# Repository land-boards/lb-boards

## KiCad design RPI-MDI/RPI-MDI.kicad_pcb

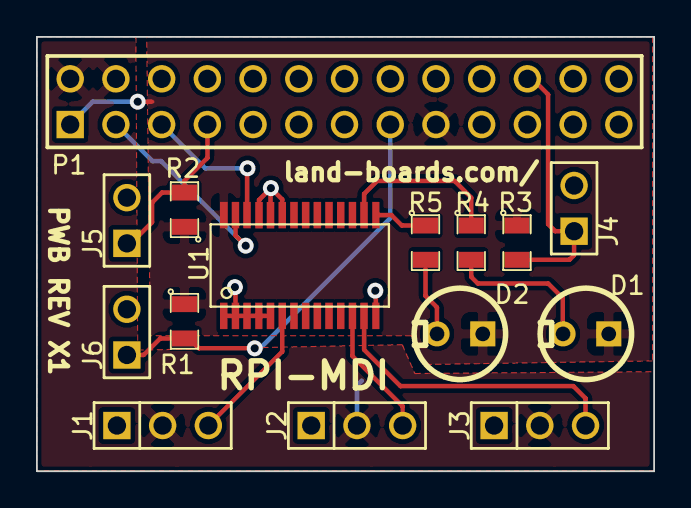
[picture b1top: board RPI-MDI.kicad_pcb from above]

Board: 2 copper layers, 34.3 x 24.1 mm, 16 parts (1 on the bottom side), 15 nets.

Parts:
C1: 106; SM1206
D1, D2: LED; LEDV
J1, J2, J3: CONN_3; PIN_ARRAY_3X1
J4, J5, J6: CONN_2; PIN_ARRAY_2X1
P1: RASPIO; pin_array_13x2
R1, R2, R3: 4.7K; SM0805
R4, R5: 120; SM0805
U1: PCA9685; tssop-28

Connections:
/+3.3V: D1.1, D2.1, P1.1, P1.17, R1.1, R2.1, R3.1, U1.28
/IO_4: J5.1, P1.7, R2.2
/IO_22: J6.1, P1.15, R1.2
/IO_25: J4.1, P1.22, R3.2
/R5: C1.1, J1.2, J2.2, J3.2, P1.2, P1.4
/SCLK1: P1.5, U1.26
/SDA1: P1.3, U1.27
GND: C1.2, J1.1, J2.1, J3.1, J4.2, J5.2, J6.2, P1.6, P1.9, P1.14, P1.20, P1.25, U1.1, U1.2, U1.3, U1.4, U1.5, U1.14, U1.23, U1.24, U1.25
unnamed: J2.3, U1.12
unnamed: J3.3, U1.13
unnamed: J1.3, U1.6
unnamed: R4.1, U1.16
unnamed: R5.1, U1.15
unnamed: D1.2, R4.2
unnamed: D2.2, R5.2

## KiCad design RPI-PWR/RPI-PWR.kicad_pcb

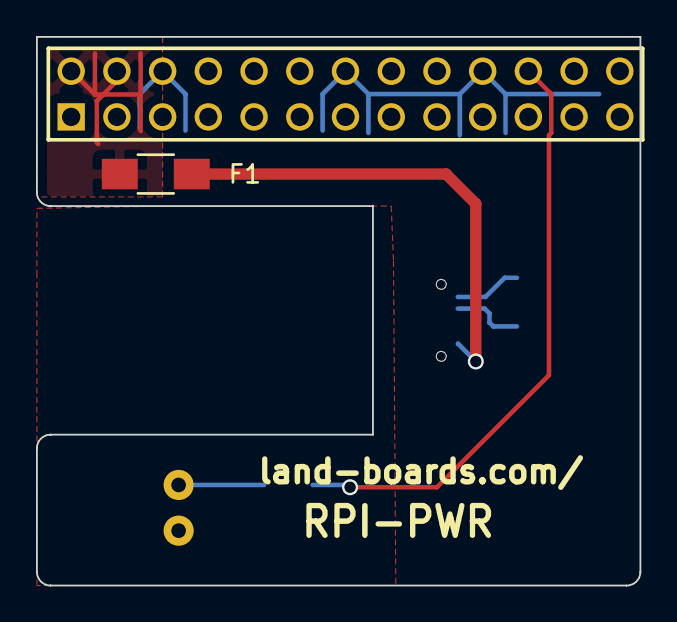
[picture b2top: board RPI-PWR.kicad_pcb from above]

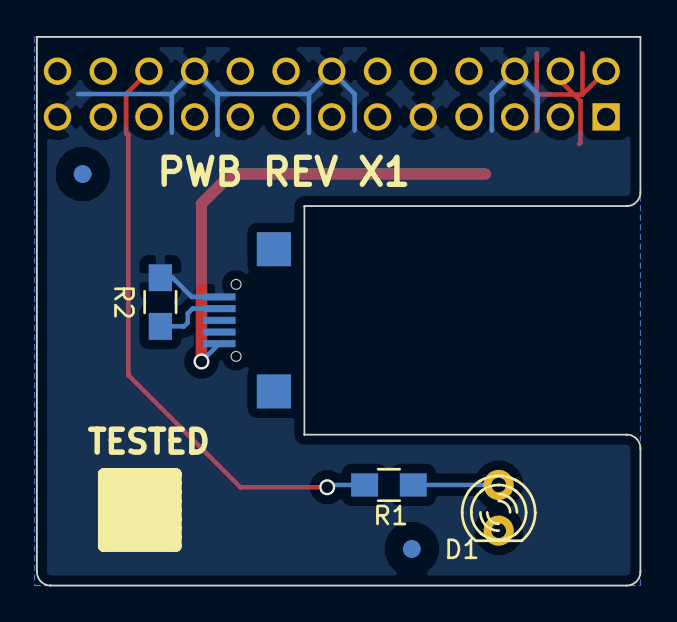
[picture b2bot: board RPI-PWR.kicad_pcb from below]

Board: 2 copper layers, 33.5 x 30.5 mm, 9 parts (7 on the bottom side), 6 nets.

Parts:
D1: LED; LED-3MM
F1: FUSE; R_1206_HandSoldering
FID1, FID2: CONN_1; FIDUCIAL
J1: USB-MICRO-B; USB_Micro-B-Wellco-SMT
J2: RASPIO; pin_array_13x2
R1: 270; R_0805_HandSoldering
R2: 130K; R_0805_HandSoldering
TESTED: COUPON; REV_BLOCK

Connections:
/+5V: F1.1, J2.2, J2.4
/+5V-USB: F1.2, J1.1
/GND: J1.5, J2.6, J2.9, J2.14, J2.20, J2.25, R2.2
/PUP0: D1.1, R1.2
unnamed: J1.4, R2.1
unnamed: J2.22, R1.1

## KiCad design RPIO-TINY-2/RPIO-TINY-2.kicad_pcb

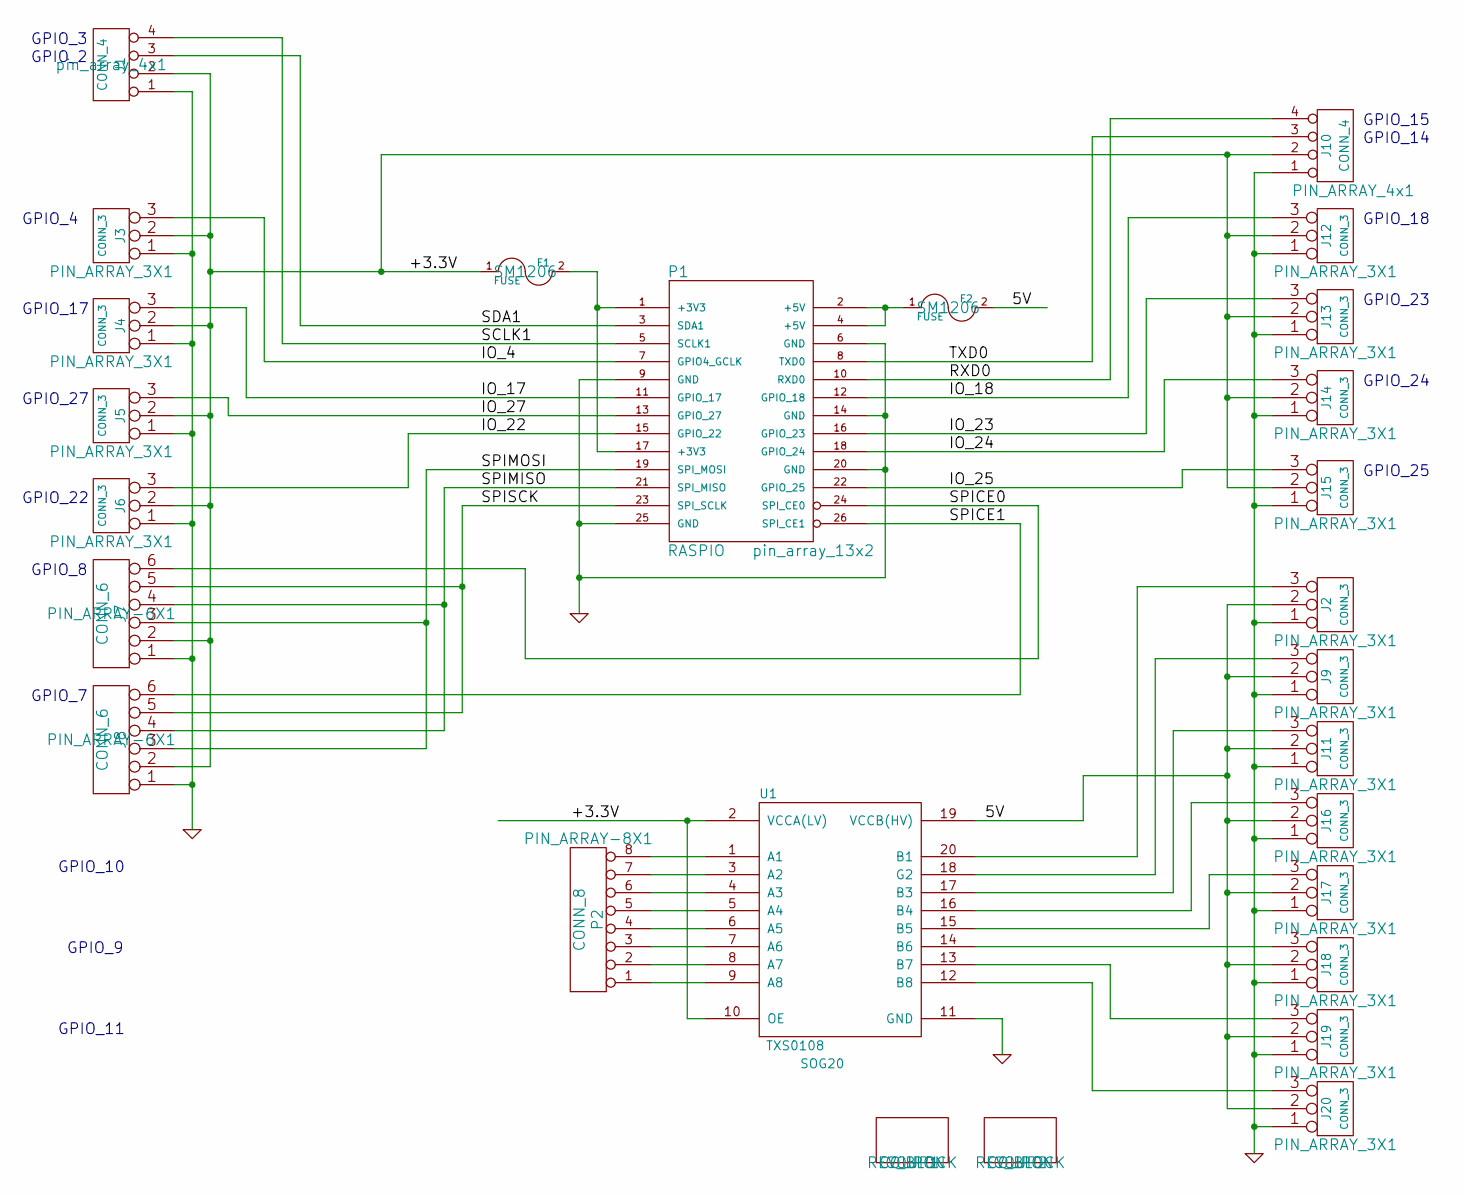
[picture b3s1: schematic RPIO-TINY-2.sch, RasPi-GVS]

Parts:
COUP1, COUP2: COUPON; REV_BLOCK
F1, F2: FUSE; SM1206
J1: CONN_4; pin_array_4x1
J2, J3, J4, J5, J6, J9, J11, J12, J13, J14, J15, J16, J17, J18, J19, J20: CONN_3; PIN_ARRAY_3X1
J7, J8: CONN_6; PIN_ARRAY-6X1
J10: CONN_4; PIN_ARRAY_4x1
P1: RASPIO; pin_array_13x2
P2: CONN_8; PIN_ARRAY-8X1
U1: TXS0108; SOG20

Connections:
/5V: F2.2, J2.2 (PM), J9.2 (PM), J11.2 (PM), J16.2 (PM), J17.2 (PM), J18.2 (PM), J19.2 (PM), J20.2 (PM), U1.19 (VCCB(HV))
/+3.3V: F1.1, J1.2, J3.2 (PM), J4.2 (PM), J5.2 (PM), J6.2 (PM), J7.2, J8.2, J10.2, J12.2 (PM), J13.2 (PM), J14.2 (PM), J15.2 (PM), U1.2 (VCCA(LV)), U1.10 (OE)
/IO_4: J3.3, P1.7 (GPIO4_GCLK)
/IO_17: J4.3, P1.11 (GPIO_17)
/IO_18: J12.3, P1.12 (GPIO_18)
/IO_22: J6.3, P1.15 (GPIO_22)
/IO_23: J13.3, P1.16 (GPIO_23)
/IO_24: J14.3, P1.18 (GPIO_24)
/IO_25: J15.3, P1.22 (GPIO_25)
/IO_27: J5.3, P1.13 (GPIO_27)
/RXD0: J10.4, P1.10 (RXD0)
/SCLK1: J1.4, P1.5 (SCLK1)
/SDA1: J1.3, P1.3 (SDA1)
/SPICE0: J7.6, P1.24 (SPI_CE0)
/SPICE1: J8.6, P1.26 (SPI_CE1)
/SPIMISO: J7.4, J8.4, P1.21 (SPI_MISO)
/SPIMOSI: J7.3, J8.3, P1.19 (SPI_MOSI)
/SPISCK: J7.5, J8.5, P1.23 (SPI_SCLK)
/TXD0: J10.3, P1.8 (TXD0)
GND: J1.1, J2.1, J3.1, J4.1, J5.1, J6.1, J7.1, J8.1, J9.1, J10.1, J11.1, J12.1, J13.1, J14.1, J15.1, J16.1, J17.1, J18.1, J19.1, J20.1, P1.6 (GND), P1.9 (GND), P1.14 (GND), P1.20 (GND), P1.25 (GND), U1.11 (GND)
unnamed: J17.3, U1.15 (B5)
unnamed: J18.3, U1.14 (B6)
unnamed: J19.3, U1.13 (B7)
unnamed: J20.3, U1.12 (B8)
unnamed: J2.3, U1.20 (B1)
unnamed: J9.3, U1.18 (G2)
unnamed: J11.3, U1.17 (B3)
unnamed: J16.3, U1.16 (B4)
unnamed: P2.3, U1.7 (A6)
unnamed: P2.1, U1.9 (A8)
unnamed: P2.2, U1.8 (A7)
unnamed: P2.4, U1.6 (A5)
unnamed: P2.5, U1.5 (A4)
unnamed: P2.6, U1.4 (A3)
unnamed: P2.7, U1.3 (A2)
unnamed: P2.8, U1.1 (A1)
unnamed: F2.1, P1.2 (+5V), P1.4 (+5V)
unnamed: F1.2, P1.1 (+3V3), P1.17 (+3V3)

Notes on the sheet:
GPIO_2
GPIO_3
GPIO_4
GPIO_17
GPIO_27
GPIO_22
GPIO_10
GPIO_9
GPIO_11
GPIO_14
GPIO_15
GPIO_18
GPIO_23
GPIO_24
GPIO_25
GPIO_8
GPIO_7

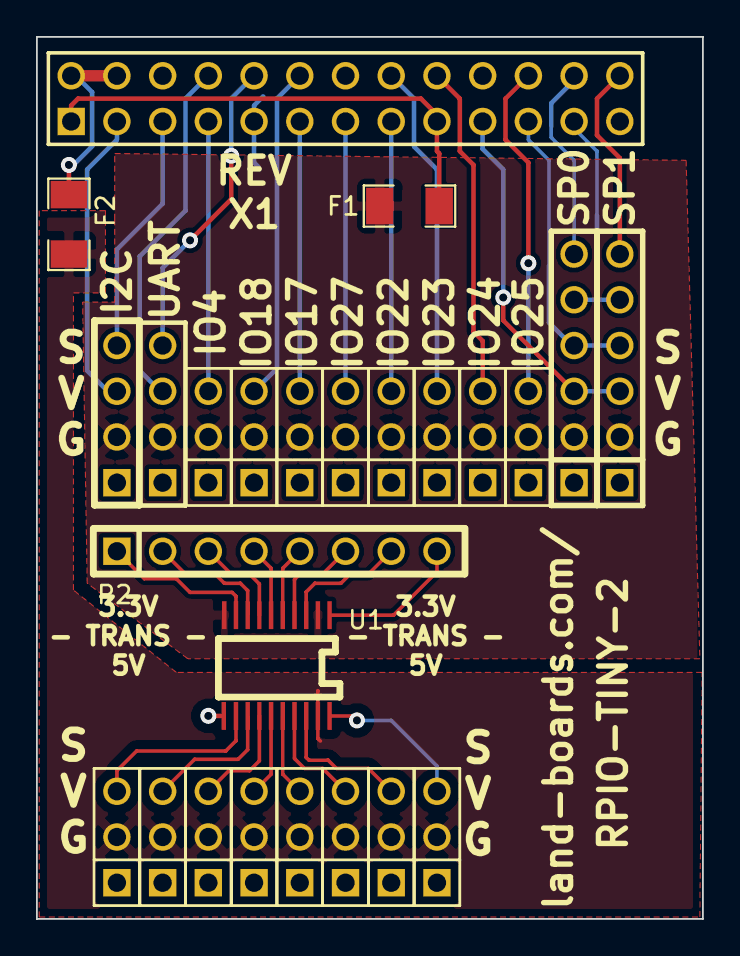
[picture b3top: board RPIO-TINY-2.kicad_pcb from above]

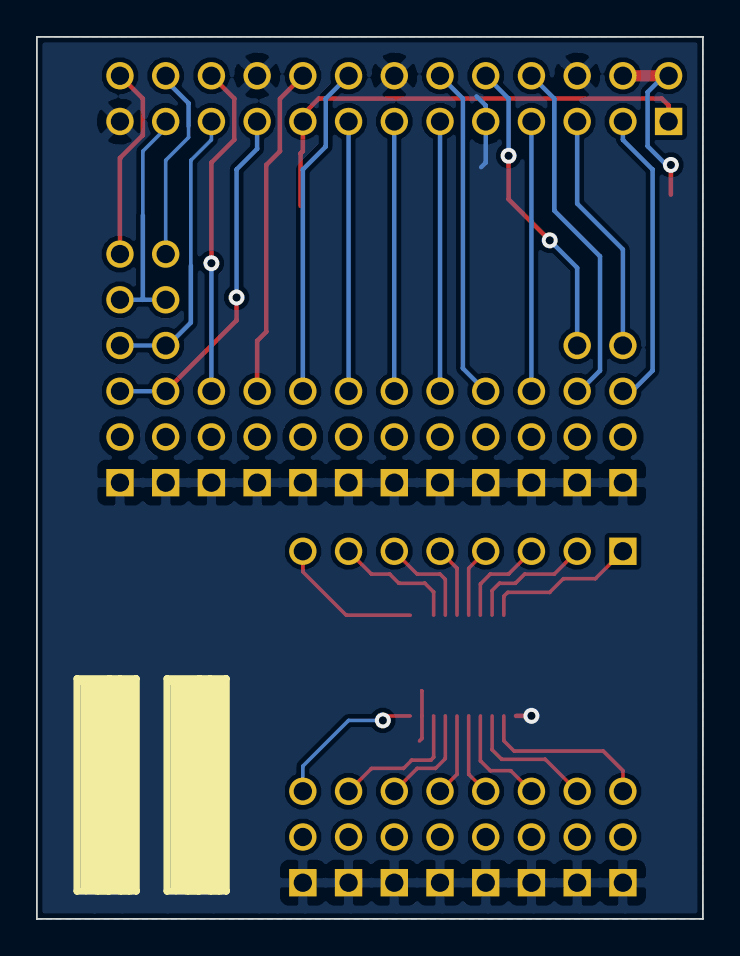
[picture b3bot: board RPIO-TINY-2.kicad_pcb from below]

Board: 2 copper layers, 37.0 x 49.0 mm, 27 parts (2 on the bottom side), 38 nets.

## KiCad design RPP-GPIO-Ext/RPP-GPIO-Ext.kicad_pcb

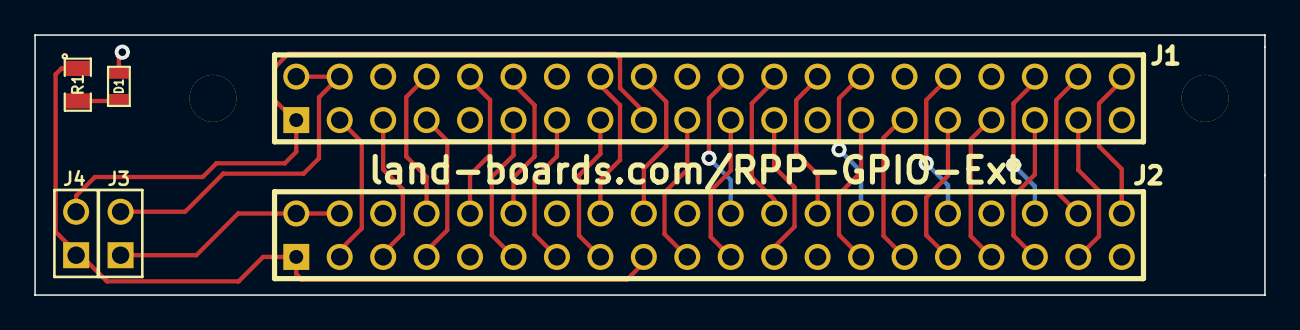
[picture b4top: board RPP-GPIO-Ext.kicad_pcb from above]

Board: 2 copper layers, 71.9 x 15.2 mm, 8 parts (0 on the bottom side), 34 nets.

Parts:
D1: LED; SM0603
J1, J2: RASPIOPLUS; PIN_ARRAY_20X2
J3, J4: CONN_2; PIN_ARRAY_2X1
MTG1, MTG2: CONN_1; MTG-2.75MM
R1: R; SM0805

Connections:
/+3.3V-1: J2.1, J2.17, J4.1, R1.1
/+3.3V-2: J1.1, J1.17, J4.2
/GND: D1.2, J1.6, J1.9, J1.14, J1.20, J1.25, J1.30, J1.34, J1.39, J2.6, J2.9, J2.14, J2.20, J2.25, J2.30, J2.34, J2.39
/ID_SC: J1.28, J2.28
/ID_SD: J1.27, J2.27
/IO_4: J1.7, J2.7
/IO_5: J1.29, J2.29
/IO_6: J1.31, J2.31
/IO_12: J1.32, J2.32
/IO_13: J1.33, J2.33
/IO_16: J1.36, J2.36
/IO_17: J1.11, J2.11
/IO_18: J1.12, J2.12
/IO_19: J1.35, J2.35
/IO_20: J1.38, J2.38
/IO_21: J1.40, J2.40
/IO_22: J1.15, J2.15
/IO_23: J1.16, J2.16
/IO_24: J1.18, J2.18
/IO_25: J1.22, J2.22
/IO_26: J1.37, J2.37
/IO_27: J1.13, J2.13
/R5-1: J2.2, J2.4, J3.1
/R5-2: J1.2, J1.4, J3.2
/RXD0: J1.10, J2.10
/SCLK1: J1.5, J2.5
/SDA1: J1.3, J2.3
/SPICE0: J1.24, J2.24
/SPICE1: J1.26, J2.26
/SPIMISO: J1.21, J2.21
/SPIMOSI: J1.19, J2.19
/SPISCK: J1.23, J2.23
/TXD0: J1.8, J2.8
unnamed: D1.1, R1.2

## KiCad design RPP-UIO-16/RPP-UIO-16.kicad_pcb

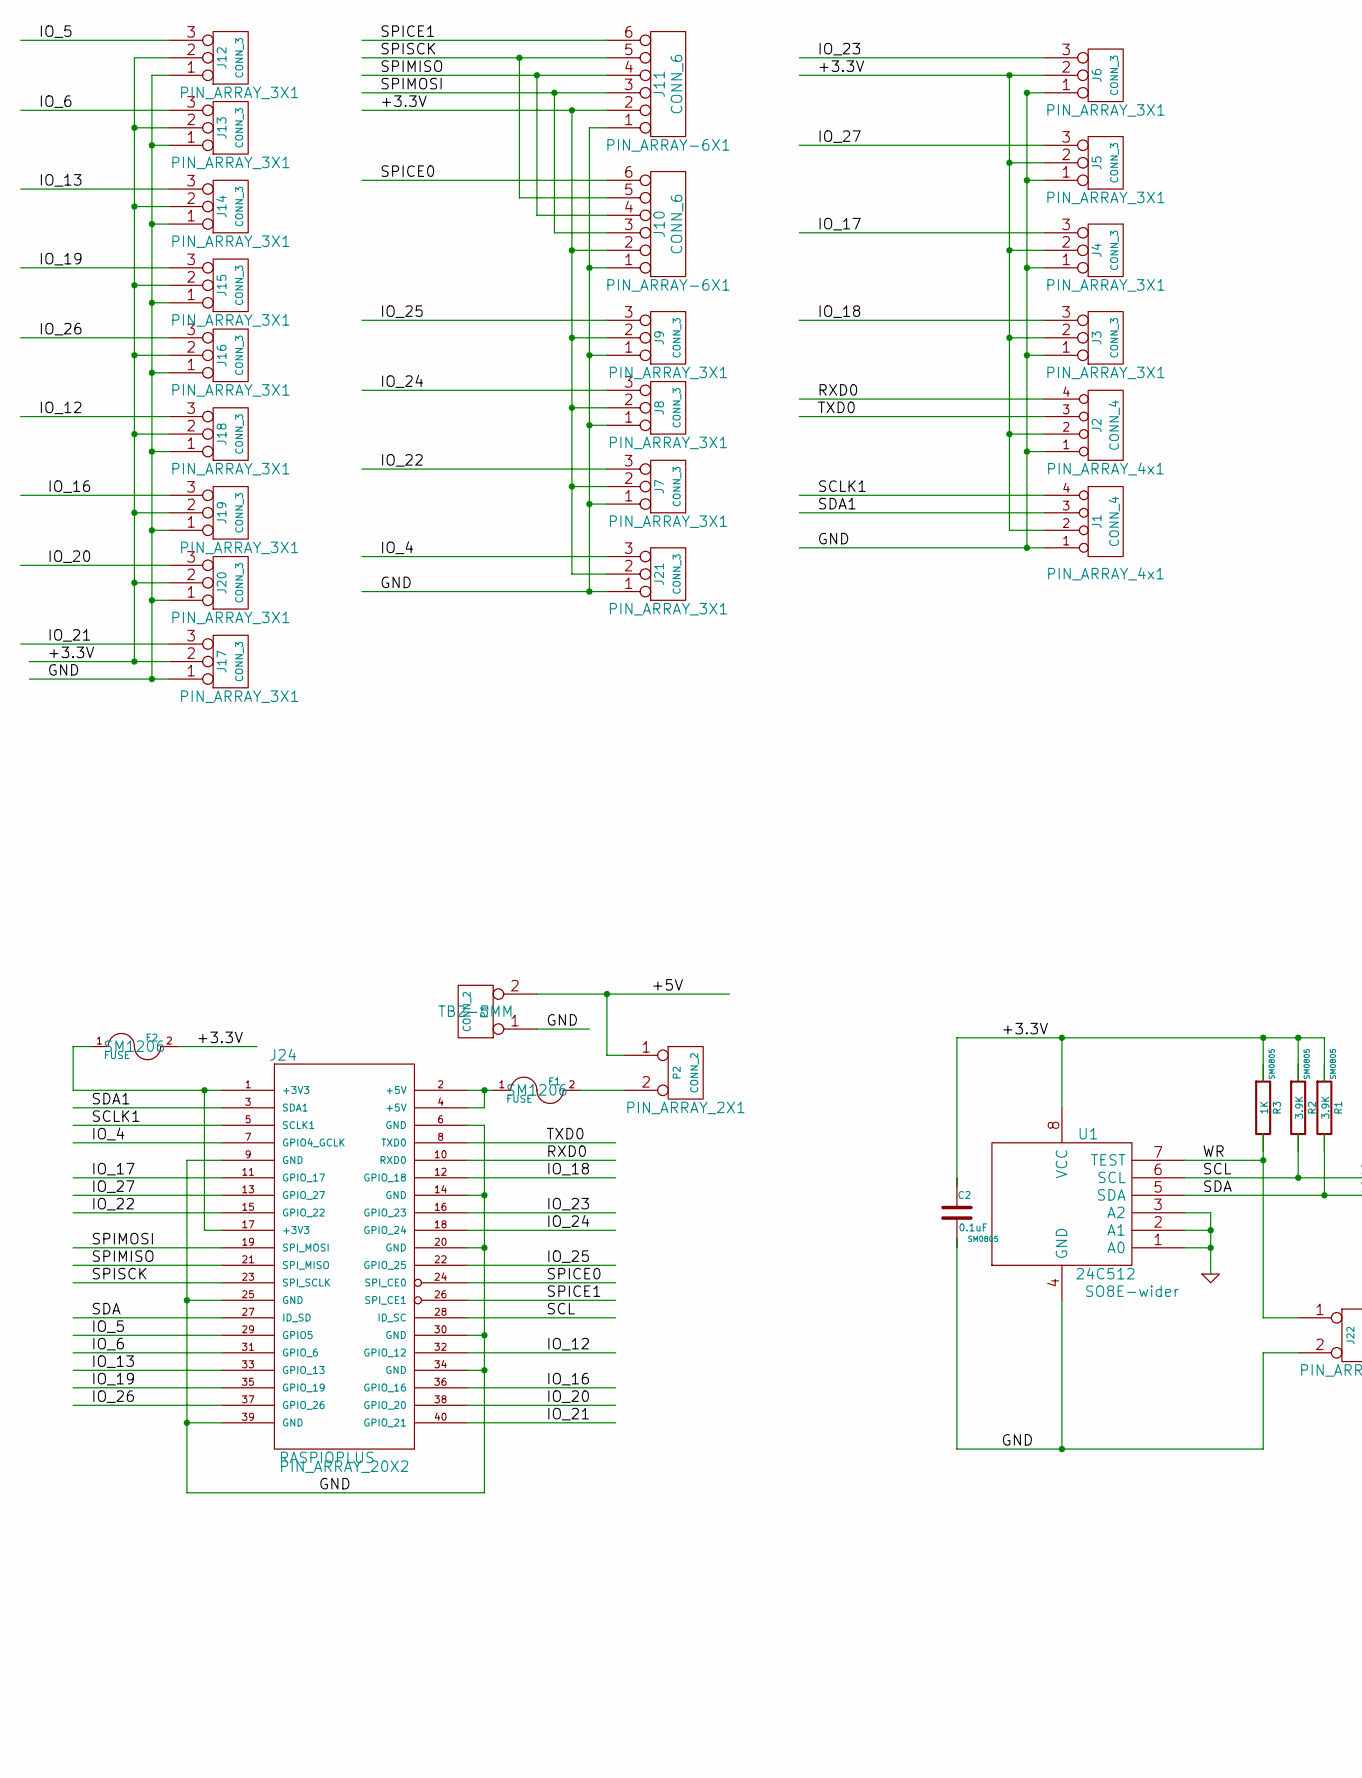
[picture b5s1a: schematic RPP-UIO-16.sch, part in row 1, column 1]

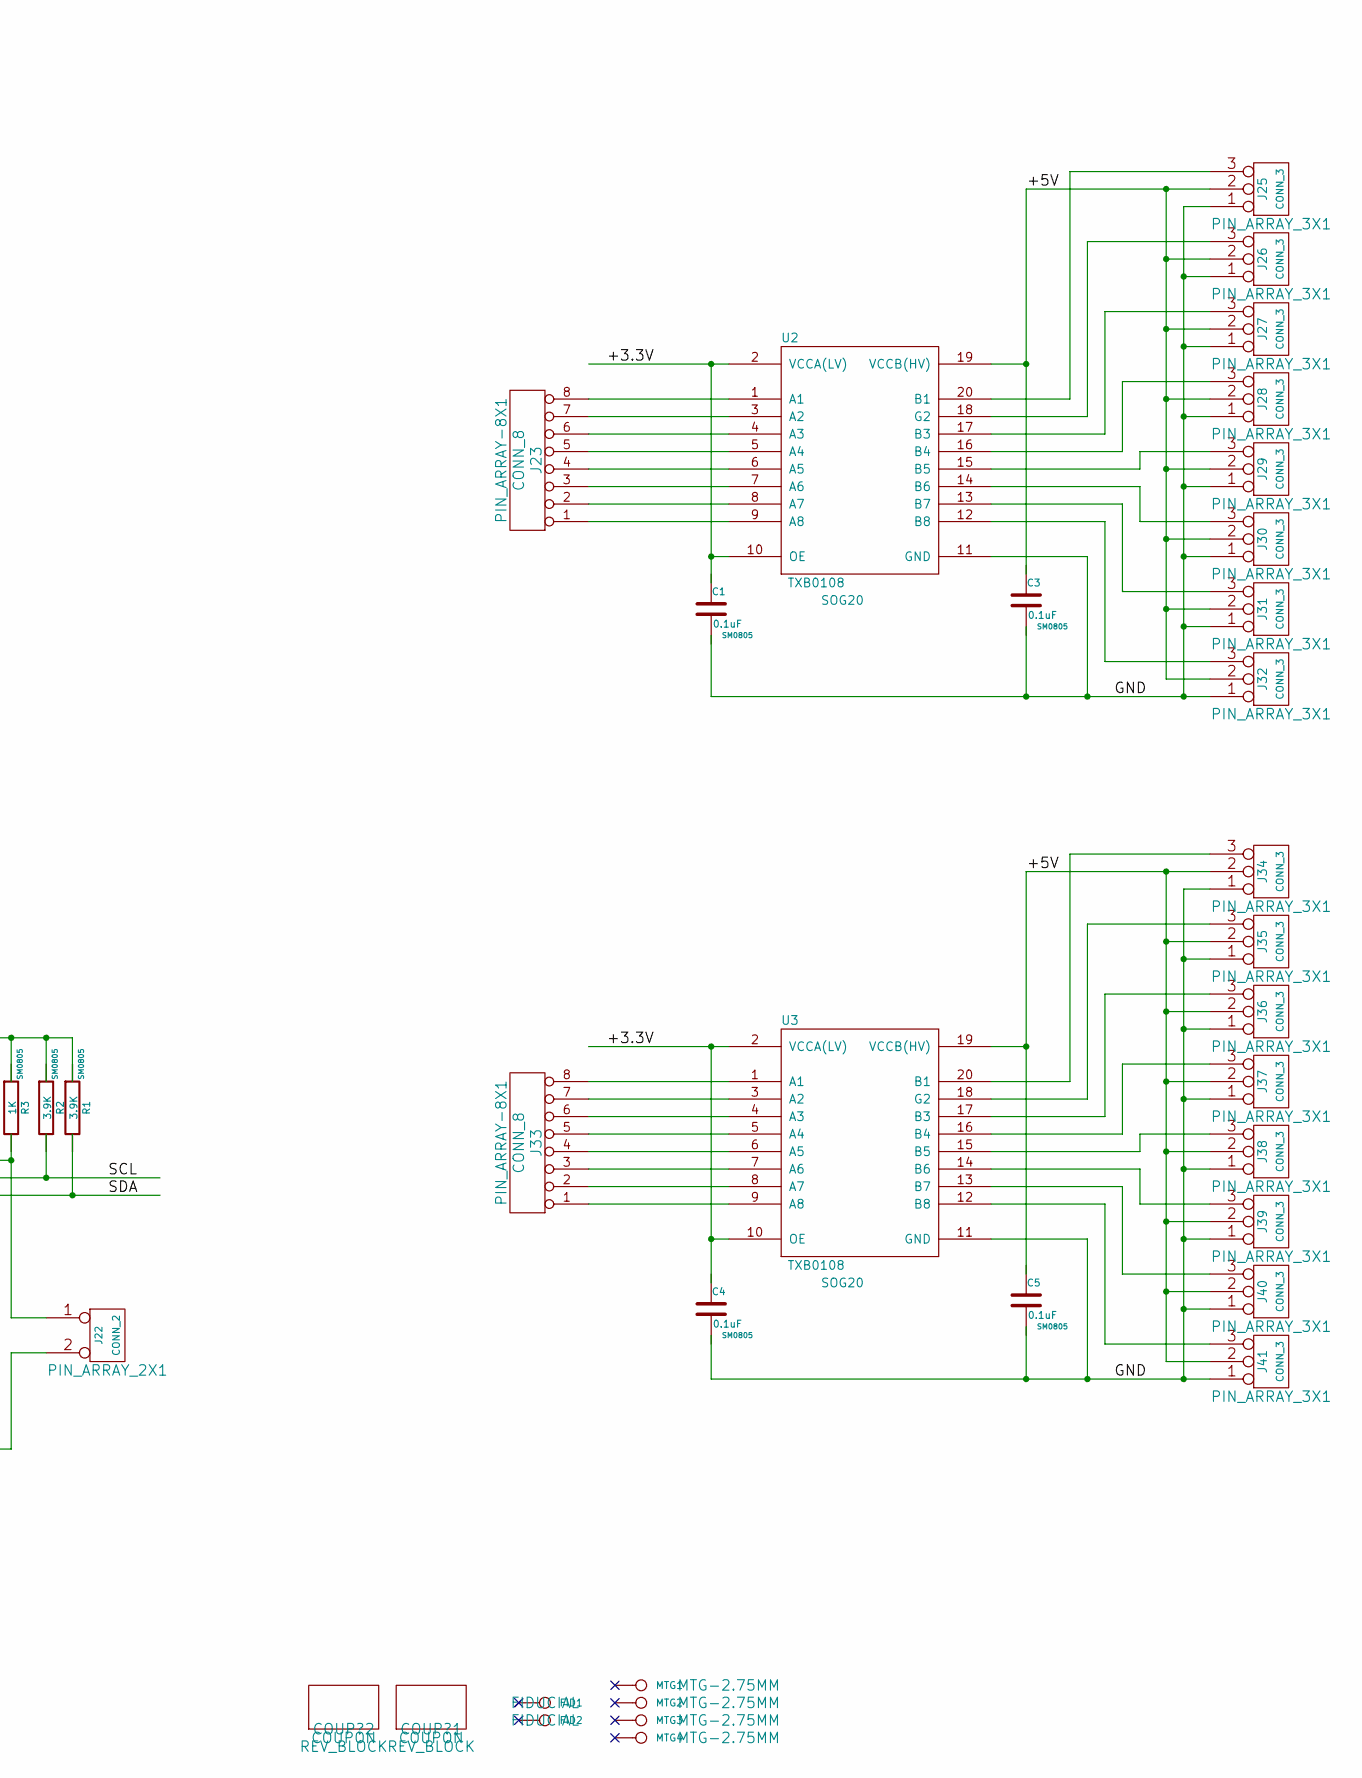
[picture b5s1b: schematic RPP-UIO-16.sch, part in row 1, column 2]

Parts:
C1, C2, C3, C4, C5: 0.1uF; SM0805
COUP?1, COUP?2: COUPON; REV_BLOCK
F1, F2: FUSE; SM1206
FID1, FID2: CONN_1; FIDUCIAL
J1, J2: CONN_4; PIN_ARRAY_4x1
J3, J4, J5, J6, J7, J8, J9, J12, J13, J14, J15, J16, J17, J18, J19, J20, J21, J25, J26, J27, J28, J29, J30, J31, J32, J34, J35, J36, J37, J38, J39, J40, J41: CONN_3; PIN_ARRAY_3X1
J10, J11: CONN_6; PIN_ARRAY-6X1
J22: CONN_2; PIN_ARRAY_2X1
J23, J33: CONN_8; PIN_ARRAY-8X1
J24: RASPIOPLUS; PIN_ARRAY_20X2
MTG1, MTG2, MTG3, MTG4: CONN_1; MTG-2.75MM
P1: CONN_2; TB2-5MM
P2: CONN_2; PIN_ARRAY_2X1
R1, R2: 3.9K; SM0805
R3: 1K; SM0805
U1: 24C512; SO8E-wider
U2, U3: TXB0108; SOG20

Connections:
/+3.3V: C1.1, C2.1, C4.1, F2.2, J1.2, J2.2, J3.2 (PM), J4.2 (PM), J5.2 (PM), J6.2 (PM), J7.2 (PM), J8.2 (PM), J9.2 (PM), J10.2, J11.2, J12.2 (PM), J13.2 (PM), J14.2 (PM), J15.2 (PM), J16.2 (PM), J17.2 (PM), J18.2 (PM), J19.2 (PM), J20.2 (PM), J21.2 (PM), R1.1, R2.1, R3.1, U1.8 (VCC), U2.2 (VCCA(LV)), U2.10 (OE), U3.2 (VCCA(LV)), U3.10 (OE)
/+5V: C3.1, C5.1, J25.2 (PM), J26.2 (PM), J27.2 (PM), J28.2 (PM), J29.2 (PM), J30.2 (PM), J31.2 (PM), J32.2 (PM), J34.2 (PM), J35.2 (PM), J36.2 (PM), J37.2 (PM), J38.2 (PM), J39.2 (PM), J40.2 (PM), J41.2 (PM), P1.2 (PM), P2.1, U2.19 (VCCB(HV)), U3.19 (VCCB(HV))
/IO_4: J21.3, J24.7 (GPIO4_GCLK)
/IO_5: J12.3, J24.29 (GPIO5)
/IO_6: J13.3, J24.31 (GPIO_6)
/IO_12: J18.3, J24.32 (GPIO_12)
/IO_13: J14.3, J24.33 (GPIO_13)
/IO_16: J19.3, J24.36 (GPIO_16)
/IO_17: J4.3, J24.11 (GPIO_17)
/IO_18: J3.3, J24.12 (GPIO_18)
/IO_19: J15.3, J24.35 (GPIO_19)
/IO_20: J20.3, J24.38 (GPIO_20)
/IO_21: J17.3, J24.40 (GPIO_21)
/IO_22: J7.3, J24.15 (GPIO_22)
/IO_23: J6.3, J24.16 (GPIO_23)
/IO_24: J8.3, J24.18 (GPIO_24)
/IO_25: J9.3, J24.22 (GPIO_25)
/IO_26: J16.3, J24.37 (GPIO_26)
/IO_27: J5.3, J24.13 (GPIO_27)
/RXD0: J2.4, J24.10 (RXD0)
/SCL: J24.28 (ID_SC), R2.2, U1.6 (SCL)
/SCLK1: J1.4, J24.5 (SCLK1)
/SDA: J24.27 (ID_SD), R1.2, U1.5 (SDA)
/SDA1: J1.3, J24.3 (SDA1)
/SPICE0: J10.6, J24.24 (SPI_CE0)
/SPICE1: J11.6, J24.26 (SPI_CE1)
/SPIMISO: J10.4, J11.4, J24.21 (SPI_MISO)
/SPIMOSI: J10.3, J11.3, J24.19 (SPI_MOSI)
/SPISCK: J10.5, J11.5, J24.23 (SPI_SCLK)
/TXD0: J2.3, J24.8 (TXD0)
/WR: J22.1, R3.2, U1.7 (TEST)
GND: C1.2, C2.2, C3.2, C4.2, C5.2, J1.1, J2.1, J3.1, J4.1, J5.1, J6.1, J7.1, J8.1, J9.1, J10.1, J11.1, J12.1, J13.1, J14.1, J15.1, J16.1, J17.1, J18.1, J19.1, J20.1, J21.1, J22.2 (PM), J24.6 (GND), J24.9 (GND), J24.14 (GND), J24.20 (GND), J24.25 (GND), J24.30 (GND), J24.34 (GND), J24.39 (GND), J25.1, J26.1, J27.1, J28.1, J29.1, J30.1, J31.1, J32.1, J34.1, J35.1, J36.1, J37.1, J38.1, J39.1, J40.1, J41.1, P1.1, U1.1 (A0), U1.2 (A1), U1.3 (A2), U1.4 (GND), U2.11 (GND), U3.11 (GND)
unnamed: F1.1, J24.2 (+5V), J24.4 (+5V)
unnamed: F1.2, P2.2 (PM)
unnamed: F2.1, J24.1 (+3V3), J24.17 (+3V3)
unnamed: J23.1, U2.9 (A8)
unnamed: J23.2, U2.8 (A7)
unnamed: J23.3, U2.7 (A6)
unnamed: J23.4, U2.6 (A5)
unnamed: J23.5, U2.5 (A4)
unnamed: J23.6, U2.4 (A3)
unnamed: J23.7, U2.3 (A2)
unnamed: J23.8, U2.1 (A1)
unnamed: J25.3, U2.20 (B1)
unnamed: J26.3, U2.18 (G2)
unnamed: J27.3, U2.17 (B3)
unnamed: J28.3, U2.16 (B4)
unnamed: J29.3, U2.15 (B5)
unnamed: J30.3, U2.14 (B6)
unnamed: J31.3, U2.13 (B7)
unnamed: J32.3, U2.12 (B8)
unnamed: J33.1, U3.9 (A8)
unnamed: J33.2, U3.8 (A7)
unnamed: J33.3, U3.7 (A6)
unnamed: J33.4, U3.6 (A5)
unnamed: J33.5, U3.5 (A4)
unnamed: J33.6, U3.4 (A3)
unnamed: J33.7, U3.3 (A2)
unnamed: J33.8, U3.1 (A1)
unnamed: J34.3, U3.20 (B1)
unnamed: J35.3, U3.18 (G2)
unnamed: J36.3, U3.17 (B3)
unnamed: J37.3, U3.16 (B4)
unnamed: J38.3, U3.15 (B5)
unnamed: J39.3, U3.14 (B6)
unnamed: J40.3, U3.13 (B7)
unnamed: J41.3, U3.12 (B8)

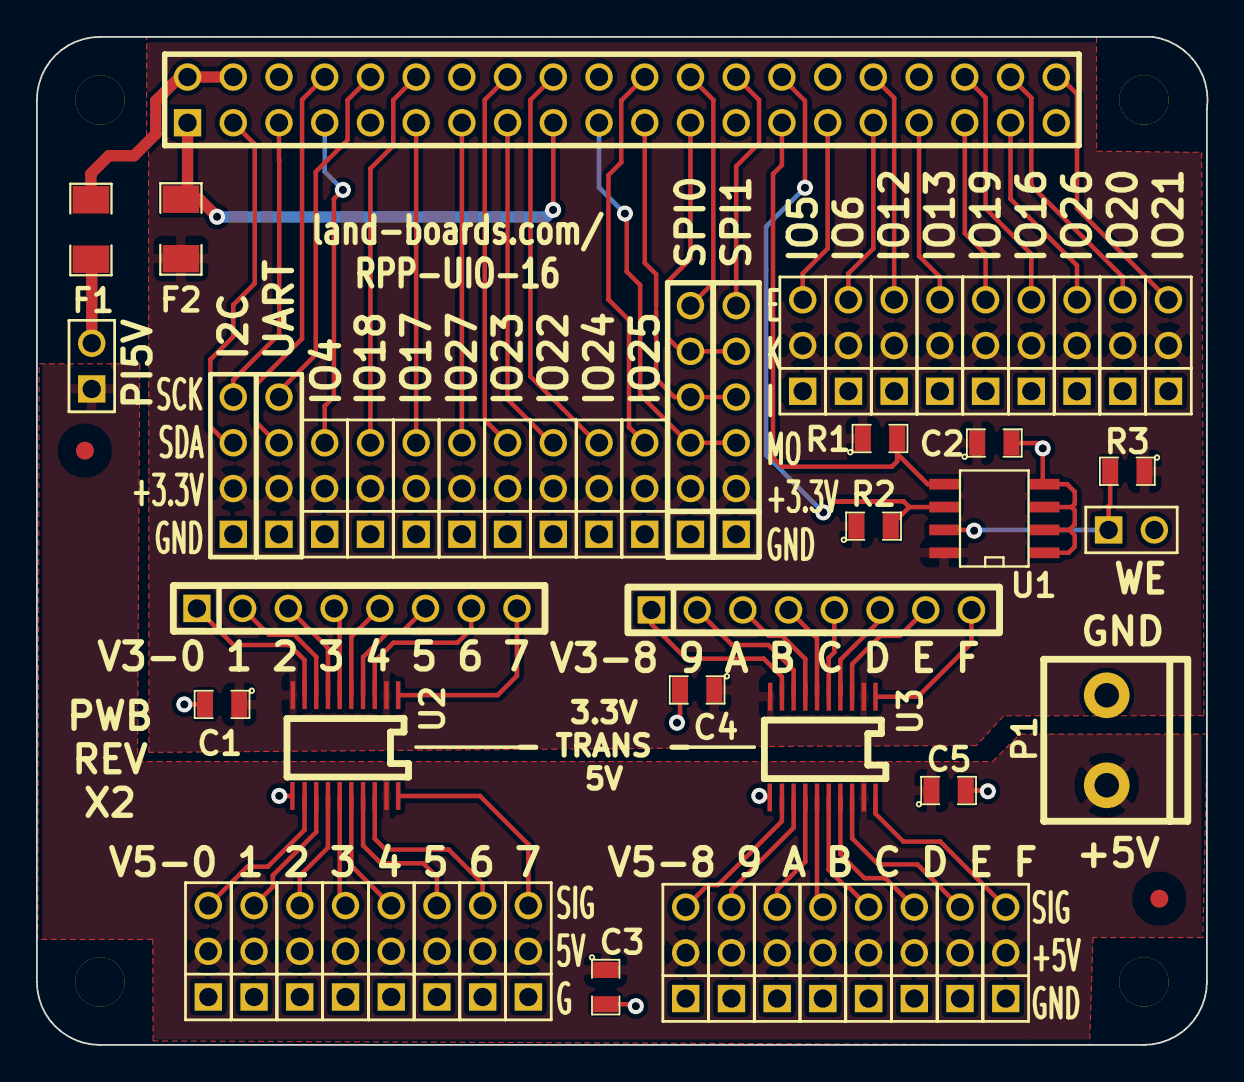
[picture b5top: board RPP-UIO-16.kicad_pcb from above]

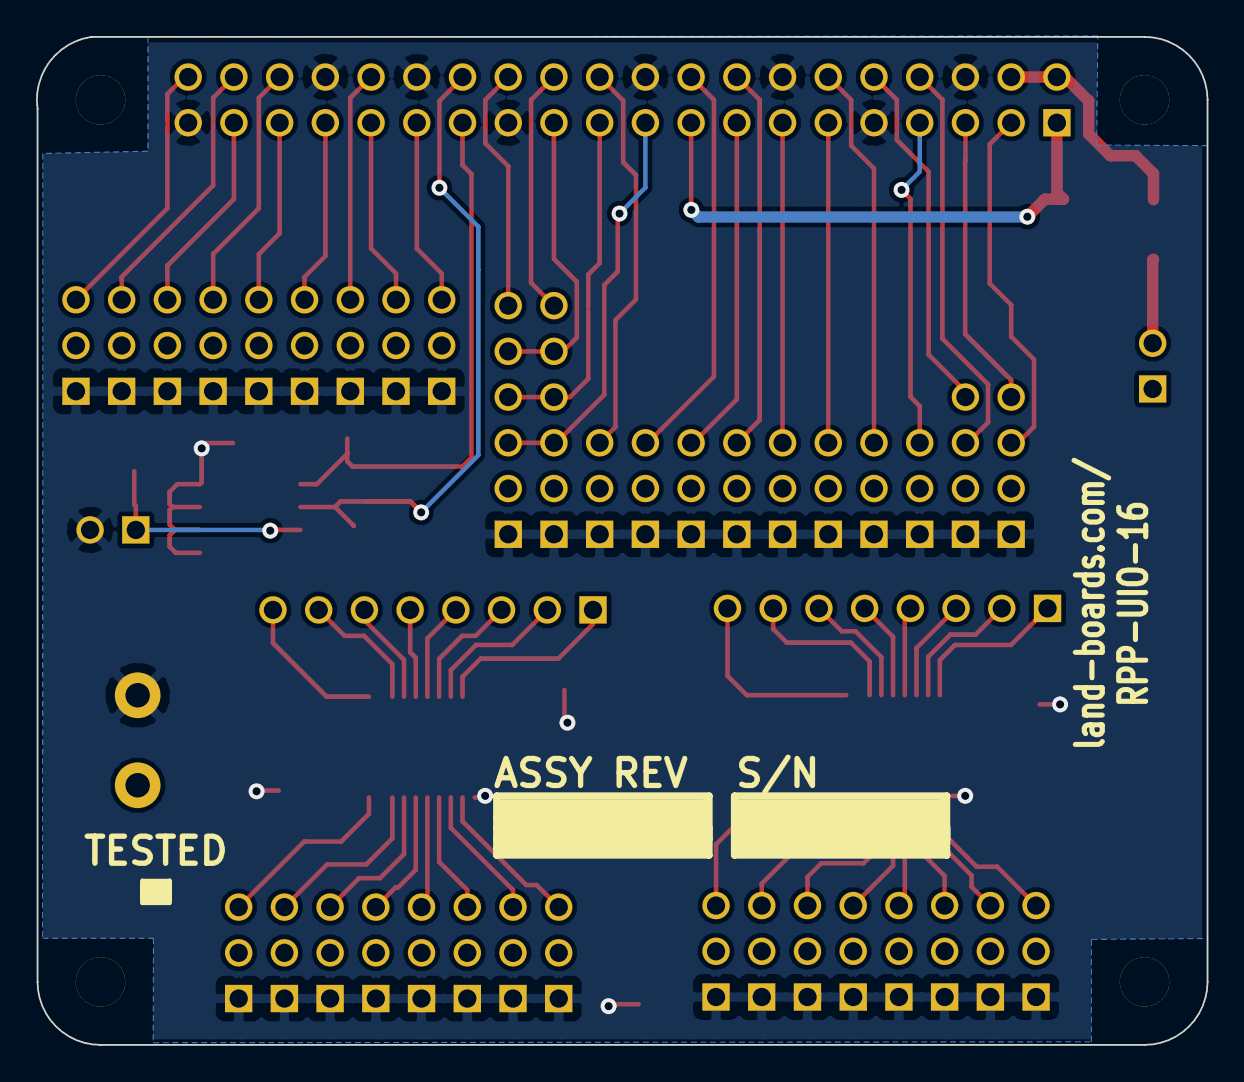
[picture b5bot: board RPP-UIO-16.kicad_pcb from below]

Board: 2 copper layers, 65.0 x 56.0 mm, 64 parts (2 on the bottom side), 67 nets.

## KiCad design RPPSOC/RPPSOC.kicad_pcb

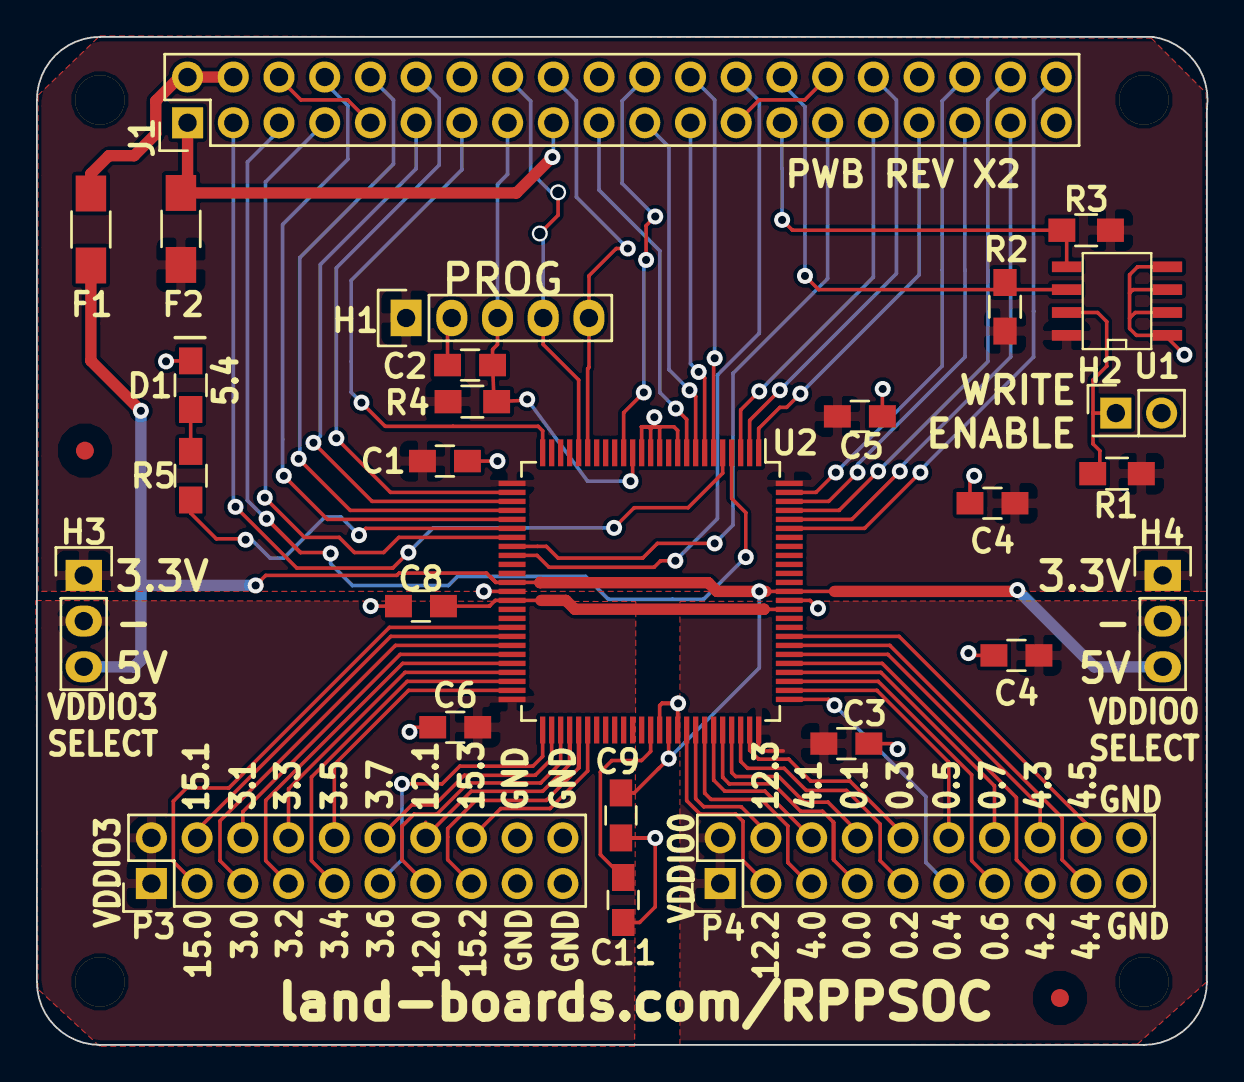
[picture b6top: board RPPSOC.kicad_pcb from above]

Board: 2 copper layers, 65.0 x 56.0 mm, 34 parts (1 on the bottom side), 70 nets.

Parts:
C1, C2, C3, C4, C5, C6, C9: 0.1uF; C_0805_HandSoldering
C4#2, C8, C11: 1uF; C_0805_HandSoldering
D1: LED; R_0805_HandSoldering
F1, F2: FUSE; R_1206_HandSoldering
FID1, FID2: CONN_1; FIDUCIAL
H1: PSOC-KITPROG; Pin_Header_Straight_1x05
H2: CONN_2; Pin_Header_Straight_2x01
H3, H4: CONN_01X03; Pin_Header_Straight_1x03
J1: RASPIOPLUS; Pin_Header_Straight_2x20
MTG1, MTG2, MTG3, MTG4: CONN_1; MTG-2.75MM
P3, P4: CONN_02X10; Pin_Header_Straight_2x10
R1: 1K; R_0805_HandSoldering
R2, R3, R4: 3.9K; R_0805_HandSoldering
R5: 120; R_0805_HandSoldering
TEST: COUPON; REV_BLOCK
U1: 24C32; SO8E-wider
U2: CY8C5267AXI-LP051; TQFP-100_14x14mm_Pitch0.5mm

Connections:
+3V3: C1.1, C4.1, C5.1, F2.2, H1.1, H3.1, H4.1, R1.1, R2.1, R3.1, R4.2, U1.8, U2.26, U2.100
+5V: C9.2, F1.2, H3.3, H4.3, U2.37, U2.65, U2.88
/IO_4: J1.7, U2.32
/IO_5: J1.29, U2.33
/IO_6: J1.31, U2.3
/IO_12: J1.32, U2.2
/IO_13: J1.33, U2.1
/IO_16: J1.36, U2.99
/IO_17: J1.11, U2.28
/IO_18: J1.12, U2.27
/IO_19: J1.35, U2.98
/IO_20: J1.38, U2.97
/IO_21: J1.40, U2.95
/IO_22: C2.1, H1.3, J1.15, R4.1, U2.15
/IO_23: H1.4, J1.16, U2.21
/IO_24: H1.5, J1.18, U2.20
/IO_25: J1.22, U2.16
/IO_26: J1.37, U2.96
/IO_27: J1.13, U2.25
/P5-4: R5.1, U2.31
/P42: P3.3, U2.42
/P43: P3.4, U2.43
/P44: P3.5, U2.44
/P45: P3.6, U2.45
/P46: P3.7, U2.46
/P47: P3.8, U2.47
/P48: P3.9, U2.48
/P49: P3.10, U2.49
/P51: P3.11, U2.51
/P52: P3.12, U2.52
/P53: P3.13, U2.53
/P54: P3.14, U2.54
/P55: P3.15, U2.55
/P56: P3.16, U2.56
/P67: P4.3, U2.67
/P68: P4.4, U2.68
/P69: P4.5, U2.69
/P70: P4.6, U2.70
/P71: P4.7, U2.71
/P72: P4.8, U2.72
/P73: P4.9, U2.73
/P74: P4.10, U2.74
/P76: P4.11, U2.76
/P77: P4.12, U2.77
/P78: P4.13, U2.78
/P79: P4.14, U2.79
/P80: P4.15, U2.80
/P81: P4.16, U2.81
/P82: P4.17, U2.82
/P83: P4.18, U2.83
/RXD0: J1.10, U2.29
/SCL: J1.28, R2.2, U1.6
/SCLK1: J1.5, U2.4
/SDA: J1.27, R3.2, U1.5
/SDA1: J1.3, U2.5
/SPICE0: J1.24, U2.6
/SPICE1: J1.26, U2.34
/SPIMISO: J1.21, U2.8
/SPIMOSI: J1.19, U2.9
/SPISCK: J1.23, U2.7
/TXD0: J1.8, U2.30
/VZ0: C3.1, C4#2.1, H4.2, P4.1, P4.2, U2.75
/VZ3: C6.1, H3.2, P3.1, P3.2, U2.50
/WR: H2.1, R1.2, U1.7
GND: C1.2, C2.2, C3.2, C4.2, C4#2.2, C5.2, C6.2, C8.1, C9.1, C11.1, D1.2, H1.2, H2.2, J1.6, J1.9, J1.14, J1.20, J1.25, J1.30, J1.34, J1.39, P3.17, P3.18, P3.19, P3.20, P4.19, P4.20, U1.1, U1.2, U1.3, U1.4, U2.10, U2.12, U2.13, U2.14, U2.38, U2.64, U2.66, U2.87
unnamed: C8.2, U2.39, U2.86
unnamed: C11.2, U2.63
unnamed: D1.1, R5.2
unnamed: F1.1, J1.2, J1.4
unnamed: F2.1, J1.1, J1.17
